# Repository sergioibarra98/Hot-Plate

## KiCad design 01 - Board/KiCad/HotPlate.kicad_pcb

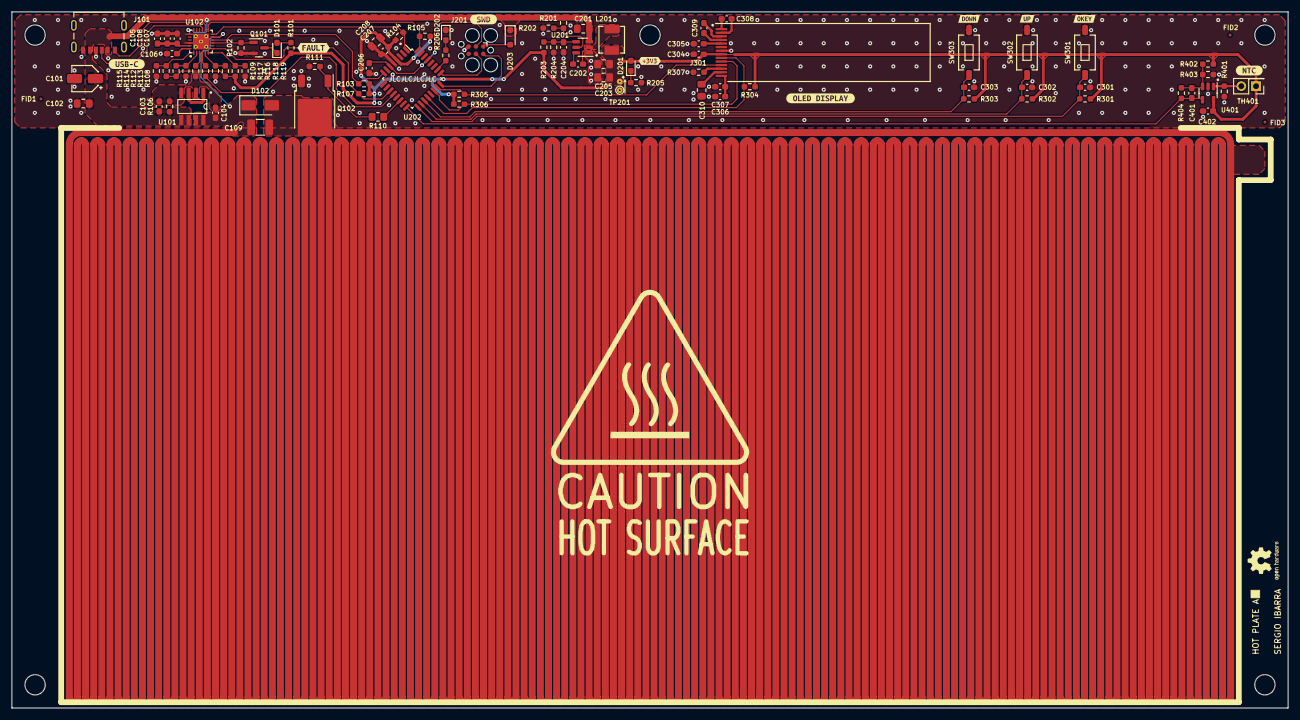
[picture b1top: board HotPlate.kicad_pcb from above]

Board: 2 copper layers, 220.0 x 120.0 mm, 96 parts (0 on the bottom side), 54 nets.

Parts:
C101: 10u; CP_Elec_4x5.4
C102, C201, C203, C205, C208, C310: 4u7; C_0805_2012Metric_Pad1.18x1.45mm_HandSolder
C103, C104, C105, C106, C301, C302, C303, C304, C305, C306, C307, C308, C309: 1u; C_0603_1608Metric_Pad1.08x0.95mm_HandSolder
C107, C108, C202, C204, C206, C207, C401, C402: 100n; C_0603_1608Metric_Pad1.08x0.95mm_HandSolder
C109: 100n; C_1210_3225Metric_Pad1.33x2.70mm_HandSolder
D101, D201, D202: RED; LED_0603_1608Metric_Pad1.05x0.95mm_HandSolder
D102: D_Schottky; D_SMA
D203: D_Schottky; D_SOD-323_HandSoldering
FID1: Fiducial_0.5mm_Mask1mm
J101: USB_C_Receptacle_PowerOnly_6P; U262-061N-4BVC11
J201: Conn_ARM_SWD_TagConnect_TC2030; Tag-Connect_TC2030-IDC-FP_2x03_P1.27mm_Vertical
J301: OLED UG-9616TSWCG02; UG-9616TSWCG02
L201: 10u; L_4.2x4.4_H2
Q101: 2N7002; SOT-23
Q102: NMOS_ALT; TO-252-2
R101, R108, R205, R206: 1k; R_0603_1608Metric_Pad0.98x0.95mm_HandSolder
R102, R106, R111, R112, R114, R116, R117, R118: 5k1; R_0603_1608Metric_Pad0.98x0.95mm_HandSolder
R103, R104, R105, R107, R109, R113, R115, R301, R302, R303, R304, R305, R306: 2k2; R_0603_1608Metric_Pad0.98x0.95mm_HandSolder
R110: 150; R_0805_2012Metric_Pad1.20x1.40mm_HandSolder
R119: 0; R_0603_1608Metric_Pad0.98x0.95mm_HandSolder
R201, R202, R204: 10k; R_0603_1608Metric_Pad0.98x0.95mm_HandSolder
R203: 33k; R_0603_1608Metric_Pad0.98x0.95mm_HandSolder
R307: 820k; R_0603_1608Metric_Pad0.98x0.95mm_HandSolder
R401: 280; R_0603_1608Metric_Pad0.98x0.95mm_HandSolder
R402: 8k2; R_0603_1608Metric_Pad0.98x0.95mm_HandSolder
R403: 5k4; R_0603_1608Metric_Pad0.98x0.95mm_HandSolder
R404: 1k5; R_0603_1608Metric_Pad0.98x0.95mm_HandSolder
SW301, SW302, SW303: SW_Push; SW_Push_1P1T_NO_3.5x8mm_H3mm
TH401: Thermistor_NTC; PinHeader_2x01_P2.54mm_Vertical
TP201: TestPoint_2Pole; TestPoint_Pad_D1.0mm_DUAL
U101: IRF9358TRPBF; SOIC-8
U102: CYPD3177; PG-VQFN-24
U201: AP62300TWU; TSOT-23-6
U202: STM32G030K8T6; LQFP-32_7x7mm_P0.8mm
U401: LM321LV; SOT-23-5
kibuzzard-64D5DEAF: G***; kibuzzard-64D5DEAF
kibuzzard-64D5E8FE: G***; kibuzzard-64D5E8FE
kibuzzard-64D73B55: G***; kibuzzard-64D73B55
kibuzzard-64D73B79: G***; kibuzzard-64D73B79
kibuzzard-64D73B89: G***; kibuzzard-64D73B89
kibuzzard-64D73C73: G***; kibuzzard-64D73C73
kibuzzard-64D50818: G***; kibuzzard-64D50818
kibuzzard-64D50885: G***; kibuzzard-64D50885
kibuzzard-64D63906: G***; kibuzzard-64D63906

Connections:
+1V8: C106.1, U102.24 (VCCD)
+3V3: C203.1, C205.1, C207.1, C208.1, C304.1, C402.2, D201.2 (A), J301.8 (VDD), L201.2, R101.1, R103.1, R104.1, R105.1, R107.1, R112.1, R114.1, R116.1, R118.1, R203.1, R301.1, R302.1, R303.1, R304.1, R305.1, R306.1, R402.1, TH401.1, TP201.2, U202.4 (VDD), U401.5 (V+)
/BUS_HEATSINK: C104.1, C109.1, C109.2, D102.1 (K), D102.2 (A), Q102.2 (D), U101.7 (D2), U101.8 (D2), U102.11 (VDC_OUT)
/CC1: J101.A5 (CC1), U102.15 (CC1)
/CC2: J101.B5 (CC2), U102.14 (CC2)
/ISNK_COARSE: R116.2, R117.1, U102.5 (ISNK_COARSE)
/ISNK_FINE: R118.2, R119.1, U102.6 (ISNK_FINE)
/LED_FAULT: Q101.1 (G), R102.1, U102.9 (FAULT)
/MCU/+3V3_EN: R201.2, R202.1, U201.5 (EN)
/MCU/BOOST: C202.1, U201.6 (BST)
/MCU/FB: C204.1, R203.2, R204.1, U201.4 (FB)
/MCU/SW: C202.2, L201.1, U201.2 (SW)
/SAFE: R109.2, U102.4
/VBUS_EN: R108.2, U102.3
/VBUS_MAX: R112.2, R113.1, U102.2 (VBUS_MAX)
/VBUS_MIN: R114.2, R115.1, U102.1 (VBUS_MIN)
BTN_DOWN: C303.1, R303.2, SW303.1, U202.19 (PA9/NC)
BTN_OKEY: C301.1, R301.2, SW301.1, U202.17 (PB2)
BTN_UP: C302.1, R302.2, SW302.1, U202.18 (PA8)
GATE_HEATER: R110.1, U202.14 (PA7)
GND: C101.2, C102.2, C105.2, C106.2, C107.2, C108.2, C201.2, C203.2, C204.2, C205.2, C206.2, C207.2, C208.2, C301.2, C302.2, C303.2, C304.2, C305.2, C306.2, C307.2, C310.2, C402.1, D202.1 (K), J101.A12 (GND), J101.B12 (GND), J201.5 (GND), J301.7 (VSS), Q101.2 (S), Q102.3 (S), R102.2, R111.2, R113.2, R115.2, R117.2, R119.2, R202.2, R204.2, R205.2, R307.2, R401.2, R403.2, SW301.2, SW302.2, SW303.2, TP201.1, U102.19 (GND), U102.22 (VSS), U102.25 (EPAD), U201.1 (GND), U202.5 (VSS), U401.2 (V-)
unnamed: D101.2 (A), R101.2
unnamed: D101.1 (K), Q101.3 (D)
unnamed: D201.1 (K), R205.1
unnamed: D202.2 (A), R206.2
unnamed: D203.2 (A), J201.1 (VCC)
unnamed: C309.2, J301.4 (C1N)
unnamed: C309.1, J301.3 (C1P)
unnamed: C308.2, J301.2 (C2N)
unnamed: C308.1, J301.1 (C2P)
unnamed: J301.12 (IREF), R307.1
unnamed: C306.1, C307.1, J301.14 (VCC)
unnamed: C310.1, J301.13 (VCOMH)
unnamed: C305.1, J301.5 (VDDB)
unnamed: Q102.1 (G), R110.2, R111.1
unnamed: C103.2, C104.2, R106.2, R108.1, U101.2 (G2), U101.4 (G1)
unnamed: U101.1 (S2), U101.3 (S1)
unnamed: R206.1, U202.26 (PA15)
unnamed: R401.1, TH401.2, U401.1 (+)
unnamed: C401.2, R402.2, R403.1, R404.1, U401.3 (-)
PD_FLIP: R103.2, U102.10 (FLIP), U202.8 (PA1)
PD_HPI: R107.2, U102.7 (HPI_INT), U202.11 (PA4)
PD_SAFE: R109.1, U202.12 (PA5)
PD_SCL: R105.2, U102.13 (HPI_SCL), U202.32 (PB8)
PD_SDA: R104.2, U102.12 (HPI_SDA), U202.1 (PB9)
SCL_OLED: J301.10 (SCL), R306.2, U202.22 (PA11/PA9)
SDA_OLED: J301.11 (SDA), R305.2, U202.23 (PA12/PA10)
SWCLK: J201.4 (SWCLK), U202.25 (PA14)
SWDIO: J201.2 (SWDIO), U202.24 (PA13)
TEMP: C401.1, R404.2, U202.16 (PB1), U401.4
VBUS: C101.1, C102.1, C103.1, C201.1, D203.1 (K), J101.A9 (VBUS), J101.B9 (VBUS), R106.1, R201.1, U101.5 (D1), U101.6 (D1), U102.18 (VBUS_IN), U201.3 (IN)
VDD: C105.1, C107.1, C108.1, U102.23 (VDDD)
~RSTn_OLED: J301.9 (RES#), R304.2, U202.20 (PC6)
~RST: C206.1, J201.3 (~RESET), U202.6 (NRST)

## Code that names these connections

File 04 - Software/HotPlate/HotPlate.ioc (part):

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Mcu.Name=STM32G030K(6-8)Tx
Mcu.Package=LQFP32
Mcu.UserName=STM32G030K8Tx
PA1.GPIOParameters=GPIO_Label
PA1.GPIO_Label=GPIO_IN_PD_FLIP
PA1.Signal=GPIO_Input
PA11\ [PA9].GPIOParameters=GPIO_Label
PA11\ [PA9].GPIO_Label=I2C_SCL_OLED
PA11\ [PA9].Mode=I2C
PA11\ [PA9].Signal=I2C2_SCL
PA12\ [PA10].GPIOParameters=GPIO_Label
PA12\ [PA10].GPIO_Label=I2C_SDA_OLED
PA12\ [PA10].Mode=I2C
PA12\ [PA10].Signal=I2C2_SDA
PA13.Mode=Serial_Wire
PA13.Signal=SYS_SWDIO
PA14-BOOT0.Mode=Serial_Wire
PA14-BOOT0.Signal=SYS_SWCLK
PA15.GPIOParameters=GPIO_Label
PA15.GPIO_Label=GPIO_LED_LIFE
PA15.Signal=GPIO_Output
PA4.GPIOParameters=GPIO_Label
PA4.GPIO_Label=GPIO_IN_INT_PD
PA4.Signal=GPIO_Input
PA5.GPIOParameters=GPIO_Label
PA5.GPIO_Label=GPIO_IN_PD_SAFE
PA5.Signal=GPIO_Input
PA7.GPIOParameters=GPIO_Label
PA7.GPIO_Label=GPIO_OUT_GATE_HEATER
PA7.Signal=GPIO_Output
PA8.GPIOParameters=GPIO_Label
PA8.GPIO_Label=GPIO_IN_BTN_UP
PA8.Signal=GPIO_Input
PA9.GPIOParameters=GPIO_Label
PA9.GPIO_Label=GPIO_IN_BTN_DOWN
PA9.Signal=GPIO_Input
PB1.GPIOParameters=GPIO_Label
PB1.GPIO_Label=ADC_IN_TEMP
PB1.Signal=SharedAnalog_PB1
PB2.GPIOParameters=GPIO_Label
PB2.GPIO_Label=GPIO_IN_BTN_OKEY
PB2.Signal=GPIO_Input
PB8.GPIOParameters=GPIO_Label
PB8.GPIO_Label=I2C_SCL_PD
PB8.Mode=I2C
PB8.Signal=I2C1_SCL
PB9.GPIOParameters=GPIO_Label
PB9.GPIO_Label=I2C_SDA_PD
PB9.Mode=I2C
PB9.Signal=I2C1_SDA
PC6.GPIOParameters=GPIO_Label
PC6.GPIO_Label=GPIO_OUT_/RST_OLED
PC6.Signal=GPIO_Output
RCC.HSE_VALUE=8000000
RCC.SYSCLKFreq_VALUE=16000000
board=custom

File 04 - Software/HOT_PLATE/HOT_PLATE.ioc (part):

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Mcu.Name=STM32G030K(6-8)Tx
Mcu.Package=LQFP32
Mcu.UserName=STM32G030K8Tx
PA11\ [PA9].GPIOParameters=GPIO_Label
PA11\ [PA9].GPIO_Label=I2C_OLED_SCL
PA11\ [PA9].Mode=I2C
PA11\ [PA9].Signal=I2C2_SCL
PA12\ [PA10].GPIOParameters=GPIO_Label
PA12\ [PA10].GPIO_Label=I2C_OLED_SDA
PA12\ [PA10].Mode=I2C
PA12\ [PA10].Signal=I2C2_SDA
PA13.Mode=Serial_Wire
PA13.Signal=SYS_SWDIO
PA14-BOOT0.Mode=Serial_Wire
PA14-BOOT0.Signal=SYS_SWCLK
PA15.GPIOParameters=GPIO_Label
PA15.GPIO_Label=GPIO_LED
PA15.Signal=GPIO_Output
PA2.GPIOParameters=GPIO_Speed,GPIO_Label
PA2.GPIO_Label=GPIO_TEST
PA2.GPIO_Speed=GPIO_SPEED_FREQ_VERY_HIGH
PA2.Signal=GPIO_Output
PA7.GPIOParameters=GPIO_Label
PA7.GPIO_Label=GATE_PWM
PA7.Signal=S_TIM3_CH2
PA8.GPIOParameters=GPIO_Label,GPIO_ModeDefaultEXTI
PA8.GPIO_Label=GPIO_BTN_UP
PA8.GPIO_ModeDefaultEXTI=GPIO_MODE_IT_FALLING
PA8.Signal=GPXTI8
PA9.GPIOParameters=GPIO_Label,GPIO_ModeDefaultEXTI
PA9.GPIO_Label=GPIO_BTN_DOWN
PA9.GPIO_ModeDefaultEXTI=GPIO_MODE_IT_FALLING
PA9.Signal=GPXTI9
PB1.GPIOParameters=GPIO_Label
PB1.GPIO_Label=ADC_NTC
PB1.Mode=IN9
PB1.Signal=ADC1_IN9
PB2.GPIOParameters=GPIO_Label,GPIO_ModeDefaultEXTI
PB2.GPIO_Label=GPIO_BTN_OK
PB2.GPIO_ModeDefaultEXTI=GPIO_MODE_IT_FALLING
PB2.Signal=GPXTI2
PB8.GPIOParameters=GPIO_Speed,GPIO_Label,GPIO_Pu
PB8.GPIO_Label=I2C_PD_SCL
PB8.GPIO_Pu=GPIO_NOPULL
PB8.GPIO_Speed=GPIO_SPEED_FREQ_LOW
PB8.Mode=I2C
PB8.Signal=I2C1_SCL
PB9.GPIOParameters=GPIO_Speed,GPIO_Label,GPIO_Pu
PB9.GPIO_Label=I2C_PD_SDA
PB9.GPIO_Pu=GPIO_NOPULL
PB9.GPIO_Speed=GPIO_SPEED_FREQ_LOW
PB9.Mode=I2C
PB9.Signal=I2C1_SDA
RCC.HSE_VALUE=8000000
RCC.SYSCLKFreq_VALUE=64000000
RCC.SYSCLKSource=RCC_SYSCLKSOURCE_PLLCLK
board=custom

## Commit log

2023-04-08 Temperature Simulation
2023-05-15 OLED Display schematic
2023-05-15 Added simulations
2023-08-11 PCB order
2023-08-11 Added 3D board
2023-11-12 Pedido
2023-11-12 Reorder files
2024-01-17 SW OLED SCREEN
2024-01-23 PI implemented
2024-01-25 SW 0.1 & updated Schematic
